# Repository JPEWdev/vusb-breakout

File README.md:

# vusb-breakout
KiCAD PCB design for a V-USB breakout board

This breadboard compatible board has all the components required for a
[V-USB][1] based project, suitable for connecting directly to the pins of an
Atmel.

Features include:

1. Voltage limiting Zener diodes on D+ and D- so the Atmel can be run anywhere
   between 3.3 and 5 V
2. Ability to be powered from USB (if jumper is set) and/or external power (via
   Vin pin). Schottky diodes prevent back-power in both cases.
3. USB ID pin is broken out

NOTE: If running the Atmel at 5V, the board will draw about 20 mA from either
D+ or D- when they are driven high.

[1]: https://www.obdev.at/products/vusb/index.html

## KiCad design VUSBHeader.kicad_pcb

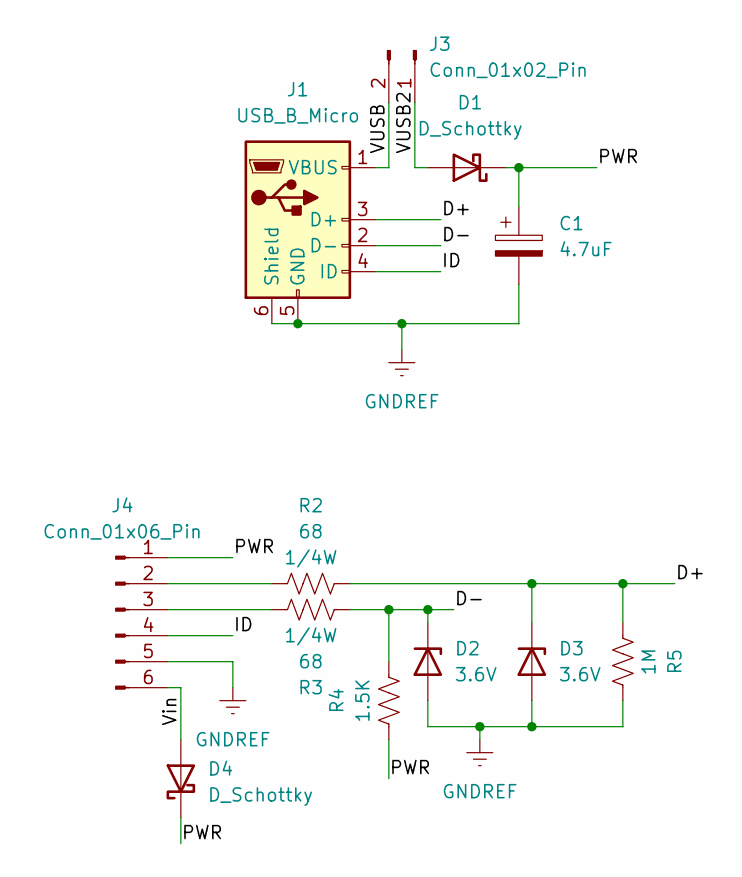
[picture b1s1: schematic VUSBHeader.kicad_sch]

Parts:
C1: 4.7uF; CP_Radial_D5.0mm_P2.50mm
D1, D4: D_Schottky; D_SOD-123
D2, D3: 3.6V; D_SOD-123
J1: USB_B_Micro; USB_Micro-B_Wuerth_629105150521
J3: Conn_01x02_Pin; PinHeader_1x02_P2.54mm_Vertical
J4: Conn_01x06_Pin; PinHeader_1x06_P2.54mm_Vertical
R2, R3: 68; R_0603_1608Metric_Pad0.98x0.95mm_HandSolder
R4: 1.5K; R_0603_1608Metric_Pad0.98x0.95mm_HandSolder
R5: 1M; R_0603_1608Metric_Pad0.98x0.95mm_HandSolder

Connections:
/D+: D3.1 (K), J1.3 (D+), R2.2, R5.2
/D-: D2.1 (K), J1.2 (D-), R3.2, R4.1
/ID: J1.4 (ID), J4.4
/PWR: C1.1, D1.1 (K), D4.1 (K), J4.1, R4.2
/VUSB: J1.1 (VBUS), J3.2
/VUSB2: D1.2 (A), J3.1
/Vin: D4.2 (A), J4.6
GNDREF: C1.2, D2.2 (A), D3.2 (A), J1.5 (GND), J1.6 (Shield), J4.5, R5.1
unnamed: J4.2, R2.1
unnamed: J4.3, R3.1

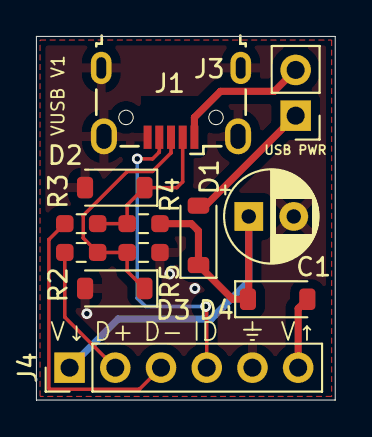
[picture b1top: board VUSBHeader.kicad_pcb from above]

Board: 2 copper layers, 16.6 x 20.2 mm, 12 parts (0 on the bottom side), 10 nets.

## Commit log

2024-12-24 Initial Commit
    Initial Commit
2024-12-31 Fix D- and D+ labeling
    The D- and D+ labels were swapped on the board, so correct them. Also
    update the README and move the manufacturing notes to make them easier
    to read
